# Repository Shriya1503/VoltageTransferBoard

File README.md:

# VoltageTransferBoard
This a custom PCB for rover to redistribute voltage for other functioning parts of it.
It steps down incoming 24V from LiPo battery into 3 parts using external Buck Converter:
5V - for ESP32, 12V - for encoders + fans and 24V (filtered) - for motors.

Schematic

Layout

3D View

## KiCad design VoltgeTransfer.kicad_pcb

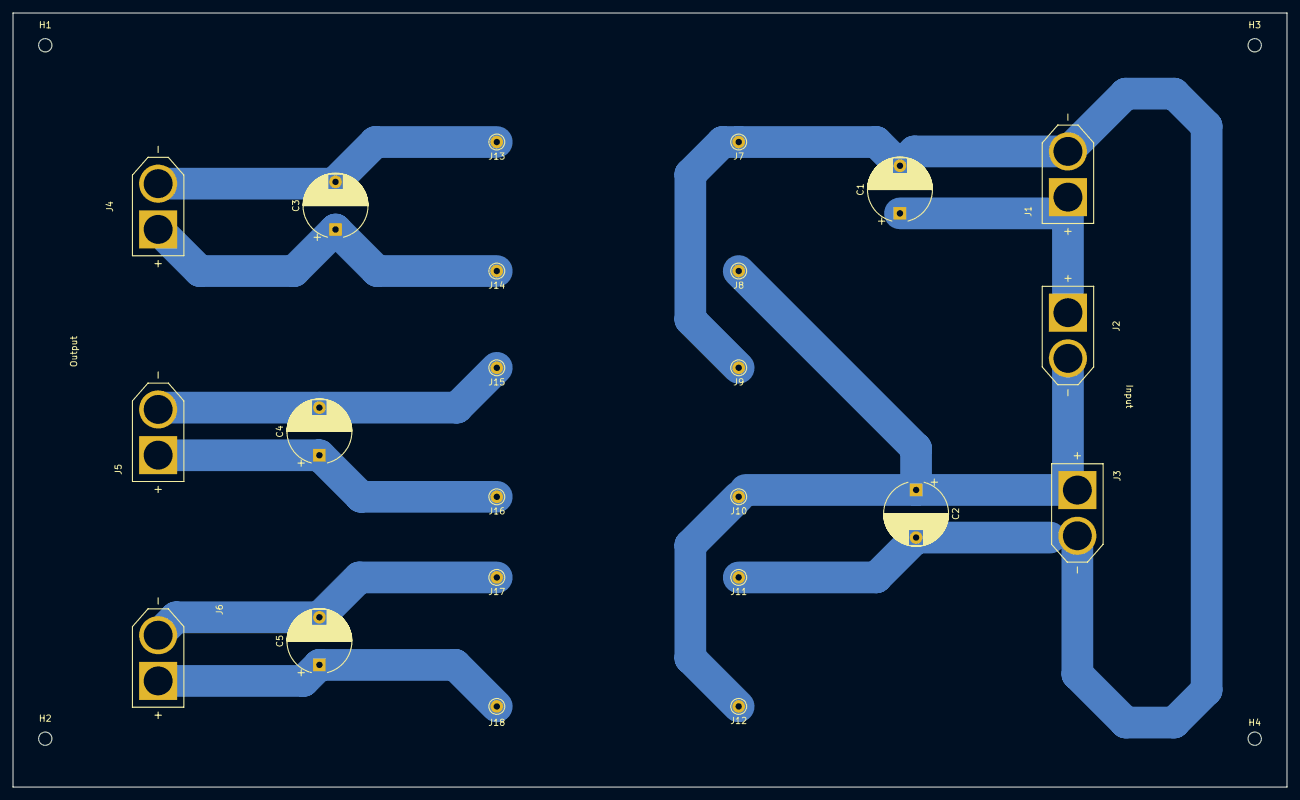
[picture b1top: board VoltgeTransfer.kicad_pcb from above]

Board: 2 copper layers, 200.7 x 121.9 mm, 27 parts (0 on the bottom side), 8 nets.

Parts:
C1, C2, C5: 50V; CP_Radial_D10.0mm_P7.50mm
C3, C4: 16V; CP_Radial_D10.0mm_P7.50mm
H1, H2, H3, H4: MountingHole; MountingHole_2.1mm
J1, J2, J3, J4, J5, J6: XT60-M; AMASS_XT60-M
J7, J8, J9, J10, J11, J12, J13, J14, J15, J16, J17, J18: Conn_01x01; Pin_D1.0mm_L10.0mm

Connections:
unnamed: C1.1, J1.P (POS), J2.P (POS)
unnamed: C2.1, J2.N (NEG), J3.P (POS), J8.1, J10.1, J12.1
unnamed: C3.2, J4.N (NEG), J13.1
unnamed: C3.1, J4.P (POS), J14.1
unnamed: C1.2, C2.2, C4.2, J1.N (NEG), J3.N (NEG), J5.N (NEG), J7.1, J9.1, J11.1, J15.1
unnamed: C4.1, J5.P (POS), J16.1
unnamed: C5.2, J6.N (NEG), J17.1
unnamed: C5.1, J6.P (POS), J18.1

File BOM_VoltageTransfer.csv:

"Source:","C:\Users\HP\Documents\Introduction\Introduction.kicad_sch"
"Date:","02-10-2024 08:37:14 PM"
"Tool:","Eeschema 7.0.10"
"Generator:","C:\Program Files\KiCad\7.0\bin\scripting\plugins/bom_csv_grouped_by_value_with_fp.py"
"Component Count:","27"
"Ref","Qnty","Value","Cmp name","Footprint","Description","Vendor","DNP"
"C1, C2, C5","3","50V","C_Polarized","Capacitor_THT:CP_Radial_D10.0mm_P7.50mm","Polarized capacitor","",""
"C3, C4","2","16V","C_Polarized","Capacitor_THT:CP_Radial_D10.0mm_P7.50mm","Polarized capacitor","",""
"H1, H2, H3, H4","4","MountingHole","MountingHole","MountingHole:MountingHole_2.1mm","Mounting Hole without connection","",""
"J1, J2, J3, J4, J5, J6","6","XT60-M","XT60-M","XT60-M:AMASS_XT60-M","","",""
"J7, J8, J9, J10, J11, J12, J13, J14, J15, J16, J17, J18","12","Conn_01x01","Conn_01x01","Connector_Pin:Pin_D1.0mm_L10.0mm","Generic connector, single row, 01x01, script generated (kicad-library-utils/schlib/autogen/connector/)","",""

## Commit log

2024-10-02 README.md
